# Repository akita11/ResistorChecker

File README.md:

# ResistorCheckerBase

M5Stack ATOMシリーズを接続し、端子間の抵抗を計測できます。抵抗値が所定の範囲に収まっているかのチェックなどに使えます。抵抗測定レンジはジャンパピンで4段階に設定できます。また小型の圧電ブザーも搭載しています。

## 使い方

FW/内のプログラムを参考に、抵抗測定値に応じた動作を記述し、それをATOMシリーズに書き込んで本機に接続し、使用します。
例としてFW/には、抵抗測定値が抵抗測定レンジ（ジャンパピンで選択した参照抵抗値）の±10%以内に収まっていれば緑点灯（440Hzの音）、それ以下であれば赤点灯（880Hzの音）、それ以上であれば紫点灯（220Hzの音）となる動作を記述してあります。

## 抵抗測定レンジの設定

測定対象の抵抗値にあわせて、抵抗測定レンジを設定することで測定精度を高めることができます。

- レンジ=L側 & 値=100側 : 100Ω
- レンジ=L側 & 値=1k側 : 1kΩ
- レンジ=H側 & 値=10k側 : 10kΩ
- レンジ=H側 & 値=100k側 : 100kΩ

## 技術的情報（測定原理）

抵抗値の測定は、本機の参照抵抗（100/1k/10k/100kからジャンパピンで選択）との分圧をATOMのアナログ入力ピンで計測しています。

測定対象の抵抗値をR、本機の参照抵抗値をRrefとすると、ATOMで測定される分圧Vmeasureは以下の式で求められます(VDD=3.3V)。この四季を使って、VmeasureからRを求めることができます。

Vmeasure = (Rref / (R + Rref) * VDD 

## Author

Junichi Akita (@akita11) / akita@ifdl.jp

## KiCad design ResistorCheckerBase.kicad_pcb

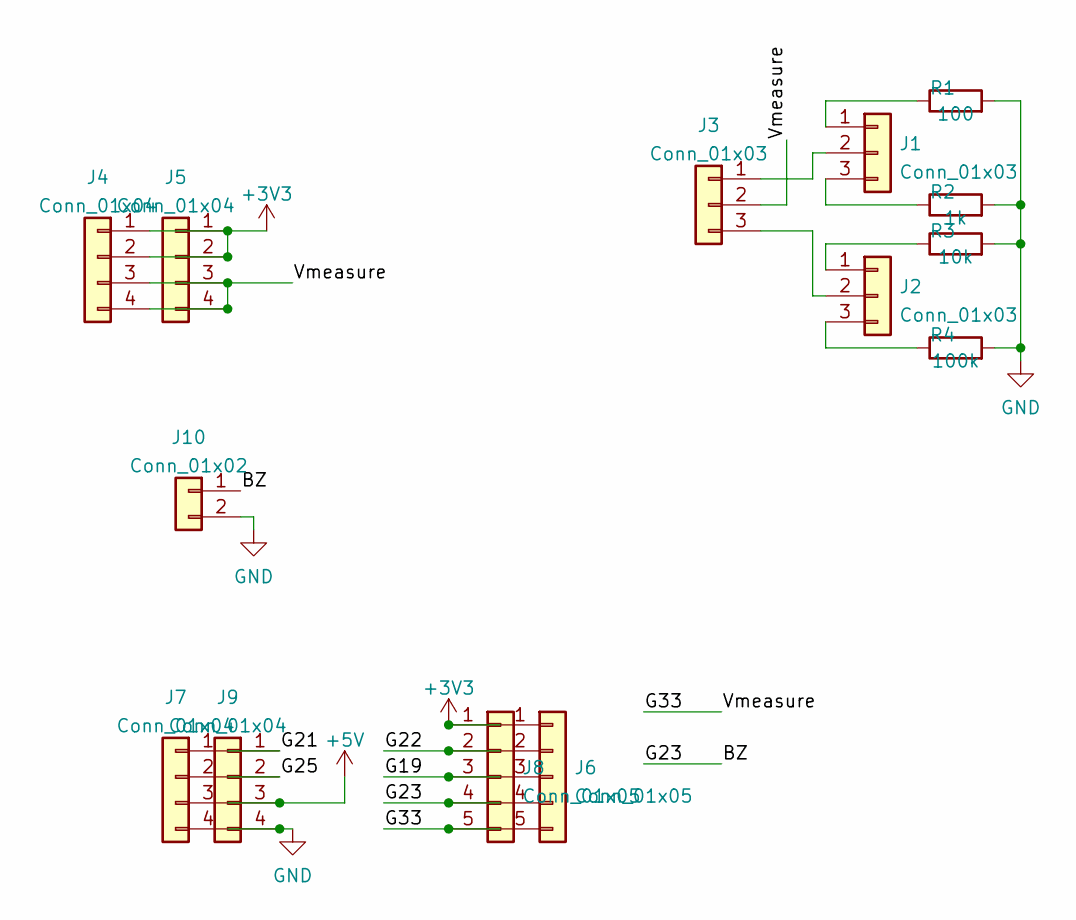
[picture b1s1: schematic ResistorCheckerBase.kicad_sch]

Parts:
J1, J2, J3: Conn_01x03; PinHeader_1x03_P2.54mm_Vertical
J4: Conn_01x04; CON_HT396R_4P_hole0.8sq
J5, J7, J9: Conn_01x04; PinHeader_1x04_P2.54mm_Vertical
J6, J8: Conn_01x05; PinHeader_1x05_P2.54mm_Vertical
J10: Conn_01x02; BZ_TSDZ5018
R1: 100; R_0603_1608Metric
R2: 1k; R_0603_1608Metric
R3: 10k; R_0603_1608Metric
R4: 100k; R_0603_1608Metric

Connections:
+3V3: J4.1, J4.2, J5.1, J5.2, J6.1, J8.1
+5V: J7.3, J9.3
/BZ: J6.4, J8.4, J10.1
/G19: J6.3, J8.3
/G21: J7.1, J9.1
/G22: J6.2, J8.2
/G25: J7.2, J9.2
/G33: J3.2, J4.3, J4.4, J5.3, J5.4, J6.5, J8.5
GND: J7.4, J9.4, J10.2, R1.2, R2.2, R3.2, R4.2
unnamed: J1.1, R1.1
unnamed: J1.2, J3.1
unnamed: J1.3, R2.1
unnamed: J2.1, R3.1
unnamed: J2.2, J3.3
unnamed: J2.3, R4.1

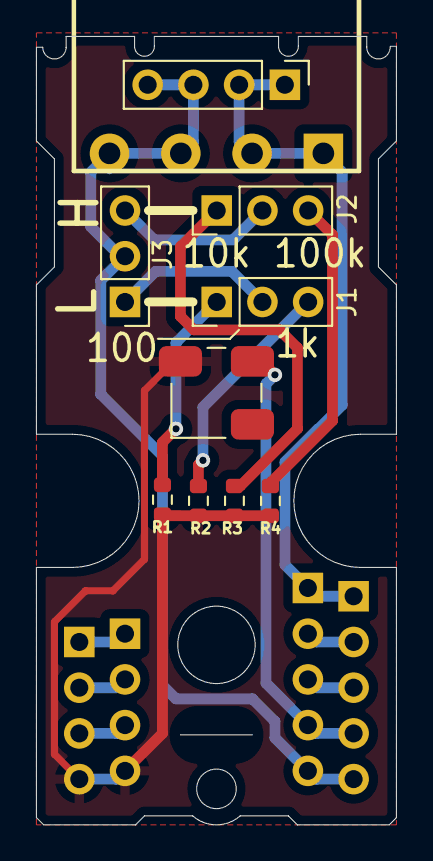
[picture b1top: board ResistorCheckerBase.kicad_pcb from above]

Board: 2 copper layers, 20.0 x 43.8 mm, 14 parts (0 on the bottom side), 15 nets.

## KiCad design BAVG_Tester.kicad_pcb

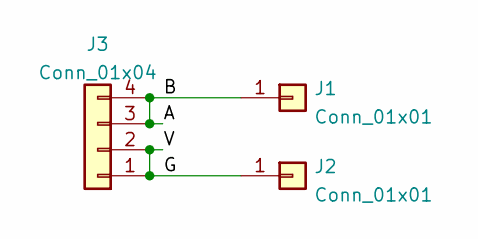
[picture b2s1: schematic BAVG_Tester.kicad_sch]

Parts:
J1, J2: Conn_01x01; CON_FCR7350
J3: Conn_01x04; CON_BAVG

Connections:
/B: J1.1, J3.3, J3.4
/G: J2.1, J3.1, J3.2

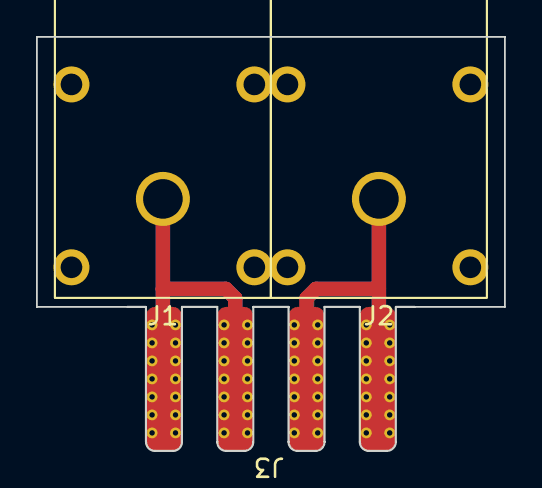
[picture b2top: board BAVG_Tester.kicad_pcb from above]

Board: 2 copper layers, 26.0 x 23.0 mm, 3 parts (0 on the bottom side), 2 nets.

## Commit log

2025-04-22 tentative FW
2025-04-27 tentarive work, tone to be fix
2025-04-27 working for ATOM Lite
2025-05-04 for Base
2025-05-11 fix defines
